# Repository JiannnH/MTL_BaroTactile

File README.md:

# MTL_BaroTactile

**A cost-efficient, repairable barometric tactile sensor**

## Highlights

- **Low cost:** material cost below **80 USD**, built from 16 MPL3115A2 MEMS barometers on a single PCB.
- **Repairable:** the rubber layer is molded **separately** rather than over the barometers, then clamped on by a 3D-printed frame, so a worn surface can be swapped in minutes.

## Sensor Design

The sensor has three layers:

1. **PCB**: 16 MPL3115A2 barometers in a 1D array, read through a multiplexer.
2. **Rubber**: a VytaFlex 40 strip cast in a 3D-printed mold.
3. **Frame**: a 3D-printed clamp bolted to the PCB that holds the rubber in place.

## Demo: Real-Time Localization on the E-TRoll Gripper

The sensor is mounted on one finger of the open-source
[**E-TRoll gripper**](https://www.imperial.ac.uk/manipulation-touch/open-source/hardware/e-troll/)
from the Manipulation and Touch Lab. The gripper rolls a cube and a cylinder across the
sensing surface, and the tactile estimate (black) closely tracks the camera-based ground truth (green).
The video plays at 10× speed.

## Repository Structure

- **[Code](Code/)**: Arduino code for the sensor (MPL3115A2) and the testing rig
- **[Hardware](Hardware/)**: PCB designs, 3D CAD files and testing rig hardware
  - **[PCB/MTL_BaroTactile_MPL3115A2](Hardware/PCB/MTL_BaroTactile_MPL3115A2/)**: main sensor version (used in the paper)
  - **[PCB/MTL_BaroTactile_MS5840](Hardware/PCB/MTL_BaroTactile_MS5840/)**: alternative version with the MS5840
  - **[Mold](Hardware/Mold/)**: rubber mold and frame CAD for fabrication
  - **[TestingRig](Hardware/TestingRig/)**: automated indentation rig for data collection

## Hardware Versions

### MPL3115A2 Version (Paper Implementation)
The primary sensor design, built with the MPL3115A2 barometric pressure sensor.

### MS5840 Version (Alternative)
An alternative design built with the MS5840 barometer. Use it when the MPL3115A2 is out of stock; it gives comparable performance for barometric tactile sensing.

## Fabrication Overview

1. 3D print the rubber mold and apply mold release spray.
2. Mix parts A and B of Smooth-On VytaFlex 40, de-gas the mixture, and pour it into the mold.
3. Close the mold and let it cure for at least 1 day, then remove the rubber.
4. Reflow-solder the components onto the PCB.
5. Place the rubber on the PCB, then bolt the 3D-printed frame over it until the rubber is held securely.

## Citation

If you use this work in your research, please cite our paper:

```bibtex
@ARTICLE{10770605,
  author={Hou, Jian and Zhou, Xin and Spiers, Adam},
  journal={IEEE Transactions on Robotics},
  title={Location and Orientation Super-Resolution Sensing With a Cost-Efficient and Repairable Barometric Tactile Sensor},
  year={2025},
  volume={41},
  pages={729-741},
  doi={10.1109/TRO.2024.3508315}
}
```

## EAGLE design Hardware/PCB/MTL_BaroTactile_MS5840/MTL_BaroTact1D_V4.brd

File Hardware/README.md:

# Hardware Design

This folder contains the hardware design files.

## Folder Structure

The repository is organized into the following folders:

**PCB Design**: This folder contains schematics and layout files for our PCB. *PCB/MTL_BaroTactile_MPL3115A2/MTL_BaroTact1D_V3* is the one we used for super-resolution. *PCB/MTL_BaroTactile_MS5840/MTL_BaroTact1D_V4* is a new PCB design, which uses the MS-5840 barometer instead of the MPL3115A2 (stopped manufacturing).

**Testing Rig Design**: In this folder, you'll find the 3D-printed components on our testing rig.

**Mold**: This folder contains CAD files related to the mold used in the manufacturing process and assembly method of rubber components and sensors within our hardware.

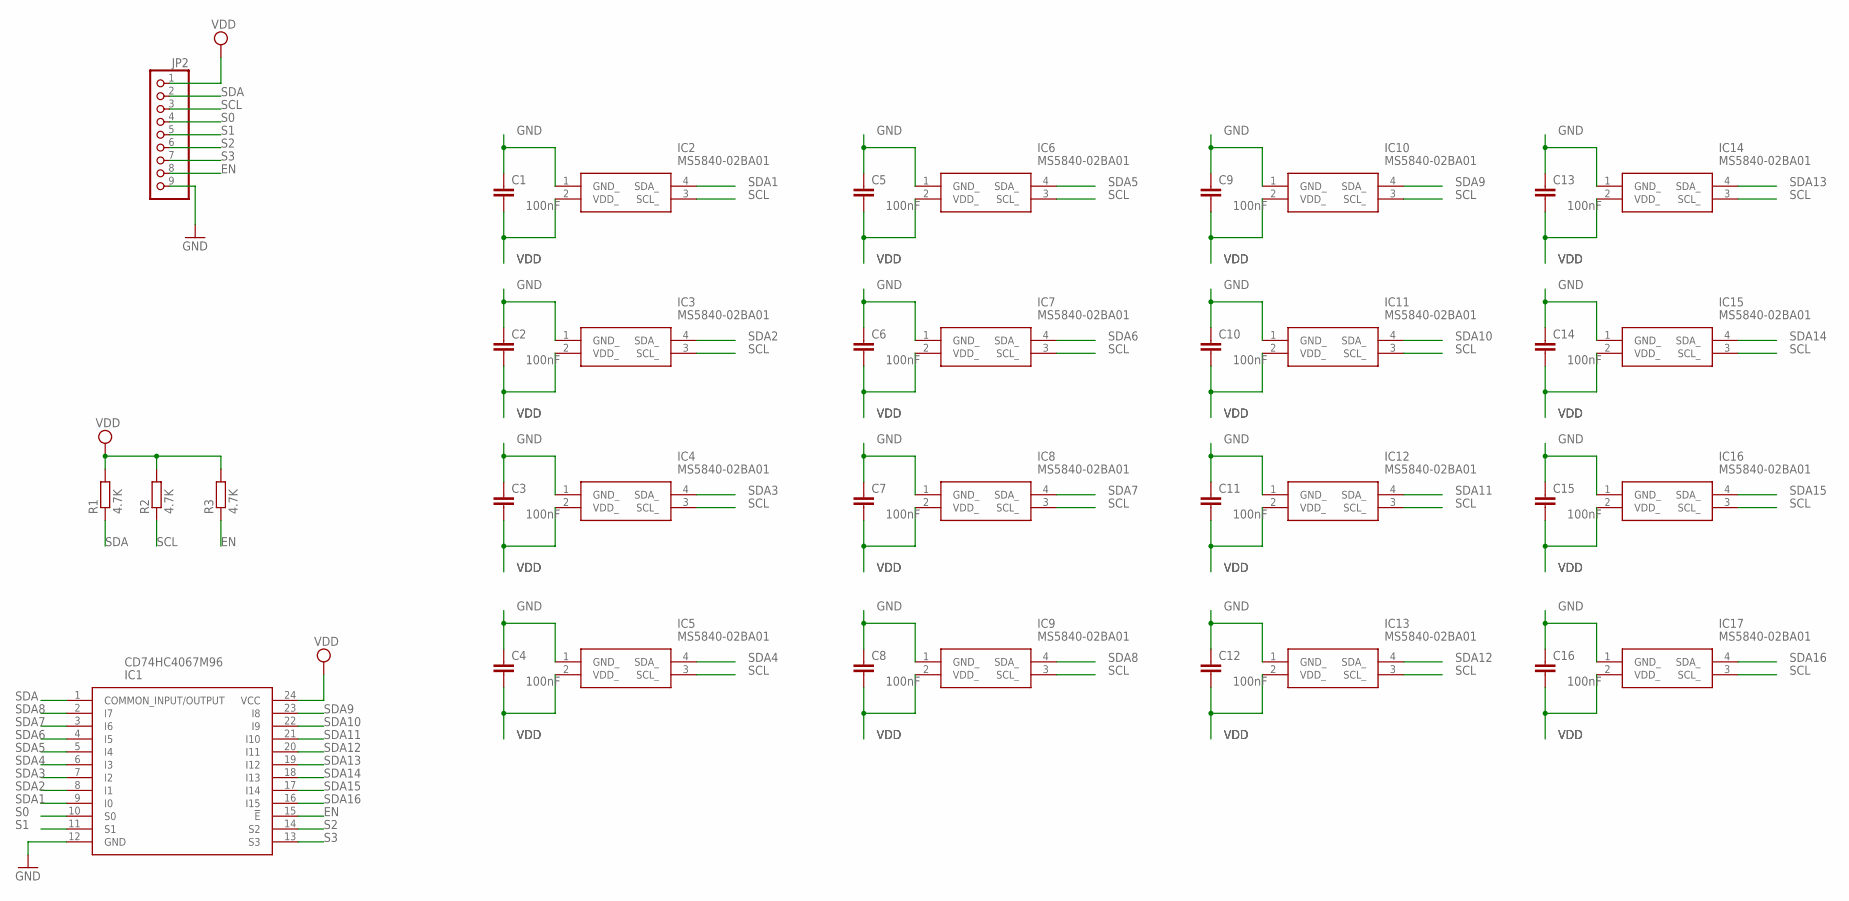
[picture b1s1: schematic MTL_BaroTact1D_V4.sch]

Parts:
C1, C2, C3, C4, C5, C6, C7, C8, C9, C10, C11, C12, C13, C14, C15, C16: 100nF; C0603
IC1: CD74HC4067M96; SOIC127P1030X265-24N
IC2, IC3, IC4, IC5, IC6, IC7, IC8, IC9, IC10, IC11, IC12, IC13, IC14, IC15, IC16, IC17: MS5840-02BA01; MS584002BA01
JP2: PINHD-1X9; 1X09
R1, R2, R3: 4.7K; R0603

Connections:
EN: IC1.15 (!E), JP2.8, R3.1
GND: C1.1, C2.1, C3.1, C4.1, C5.1, C6.1, C7.1, C8.1, C9.1, C10.1, C11.1, C12.1, C13.1, C14.1, C15.1, C16.1, IC1.12 (GND), IC2.1 (GND_), IC3.1 (GND_), IC4.1 (GND_), IC5.1 (GND_), IC6.1 (GND_), IC7.1 (GND_), IC8.1 (GND_), IC9.1 (GND_), IC10.1 (GND_), IC11.1 (GND_), IC12.1 (GND_), IC13.1 (GND_), IC14.1 (GND_), IC15.1 (GND_), IC16.1 (GND_), IC17.1 (GND_), JP2.9
S0: IC1.10 (S0), JP2.4
S1: IC1.11 (S1), JP2.5
S2: IC1.14 (S2), JP2.6
S3: IC1.13 (S3), JP2.7
SCL: IC2.3 (SCL_), IC3.3 (SCL_), IC4.3 (SCL_), IC5.3 (SCL_), IC6.3 (SCL_), IC7.3 (SCL_), IC8.3 (SCL_), IC9.3 (SCL_), IC10.3 (SCL_), IC11.3 (SCL_), IC12.3 (SCL_), IC13.3 (SCL_), IC14.3 (SCL_), IC15.3 (SCL_), IC16.3 (SCL_), IC17.3 (SCL_), JP2.3, R2.1
SDA: IC1.1 (COMMON_INPUT/OUTPUT), JP2.2, R1.1
SDA1: IC1.9 (I0), IC2.4 (SDA_)
SDA2: IC1.8 (I1), IC3.4 (SDA_)
SDA3: IC1.7 (I2), IC4.4 (SDA_)
SDA4: IC1.6 (I3), IC5.4 (SDA_)
SDA5: IC1.5 (I4), IC6.4 (SDA_)
SDA6: IC1.4 (I5), IC7.4 (SDA_)
SDA7: IC1.3 (I6), IC8.4 (SDA_)
SDA8: IC1.2 (I7), IC9.4 (SDA_)
SDA9: IC1.23 (I8), IC10.4 (SDA_)
SDA10: IC1.22 (I9), IC11.4 (SDA_)
SDA11: IC1.21 (I10), IC12.4 (SDA_)
SDA12: IC1.20 (I11), IC13.4 (SDA_)
SDA13: IC1.19 (I12), IC14.4 (SDA_)
SDA14: IC1.18 (I13), IC15.4 (SDA_)
SDA15: IC1.17 (I14), IC16.4 (SDA_)
SDA16: IC1.16 (I15), IC17.4 (SDA_)
VDD: C1.2, C2.2, C3.2, C4.2, C5.2, C6.2, C7.2, C8.2, C9.2, C10.2, C11.2, C12.2, C13.2, C14.2, C15.2, C16.2, IC1.24 (VCC), IC2.2 (VDD_), IC3.2 (VDD_), IC4.2 (VDD_), IC5.2 (VDD_), IC6.2 (VDD_), IC7.2 (VDD_), IC8.2 (VDD_), IC9.2 (VDD_), IC10.2 (VDD_), IC11.2 (VDD_), IC12.2 (VDD_), IC13.2 (VDD_), IC14.2 (VDD_), IC15.2 (VDD_), IC16.2 (VDD_), IC17.2 (VDD_), JP2.1, R1.2, R2.2, R3.2

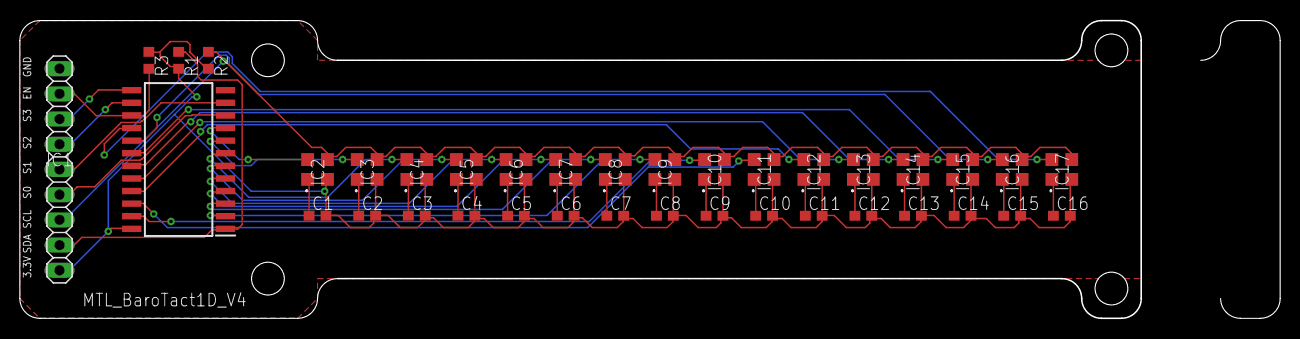
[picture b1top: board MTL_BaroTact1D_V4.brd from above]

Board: 2 copper layers, 126.8 x 30.0 mm, 37 parts (0 on the bottom side), 25 nets.

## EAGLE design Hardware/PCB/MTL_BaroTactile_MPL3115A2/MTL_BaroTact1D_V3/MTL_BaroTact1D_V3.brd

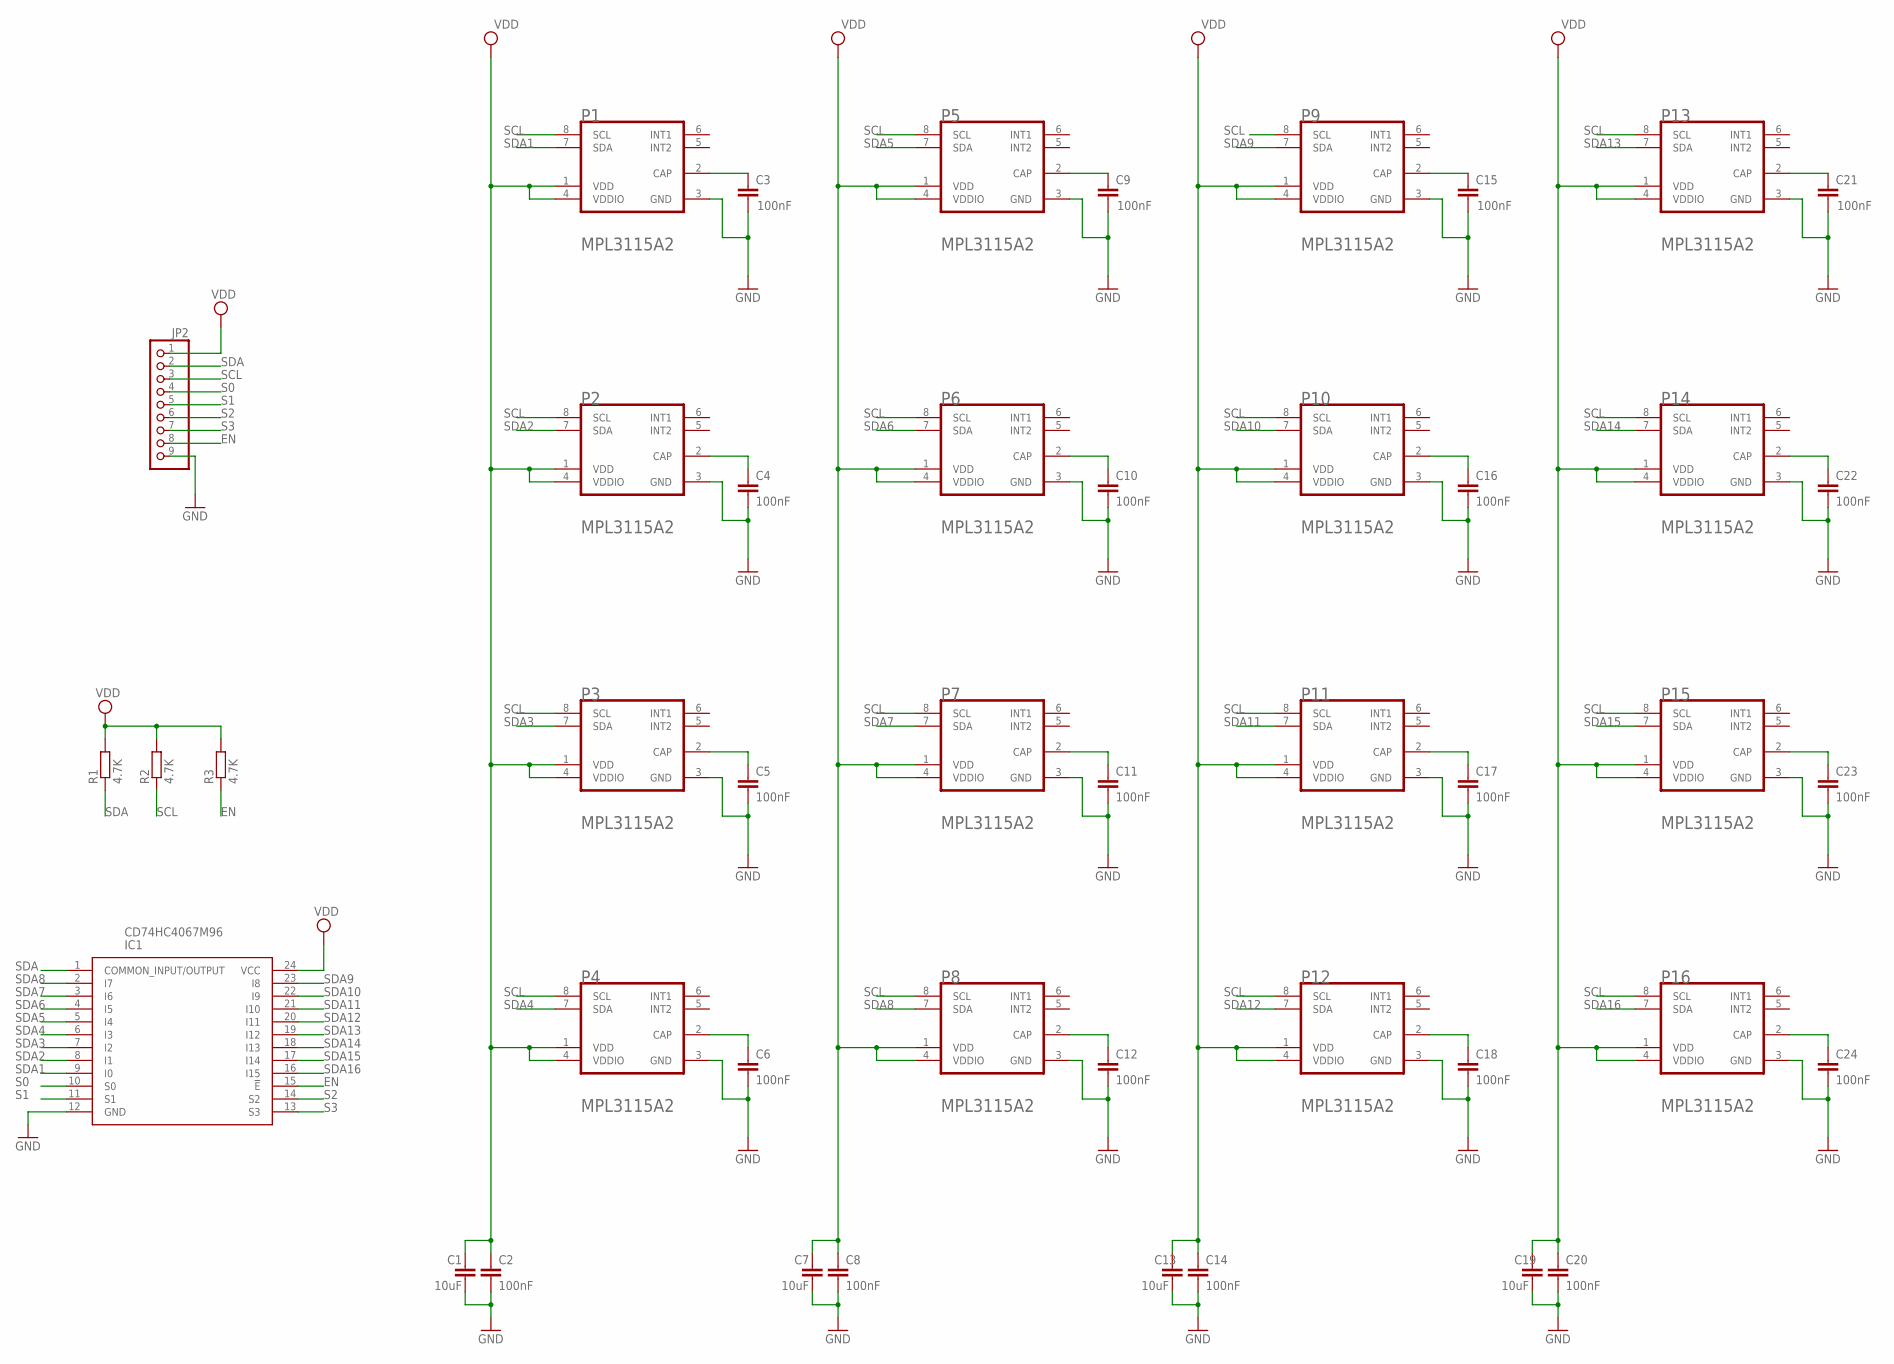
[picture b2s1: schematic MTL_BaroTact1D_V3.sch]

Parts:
C1, C7, C13, C19: 10uF; C0603
C2, C3, C4, C5, C6, C8, C9, C10, C11, C12, C14, C15, C16, C17, C18, C20, C21, C22, C23, C24: 100nF; C0603
IC1: CD74HC4067M96; SOIC127P1030X265-24N
JP2: PINHD-1X9; 1X09
P1, P2, P3, P4, P5, P6, P7, P8, P9, P10, P11, P12, P13, P14, P15, P16: FREESCALE_SEMICONDUCTOR_MPL3115A2FREESCALE_SEMICO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; FREESCALE_SEMICONDUCTOR_MPL3115A2_0
R1, R2, R3: 4.7K; R0603

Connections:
EN: IC1.15 (!E), JP2.8, R3.1
GND: C1.2, C2.2, C3.2, C4.2, C5.2, C6.2, C7.2, C8.2, C9.2, C10.2, C11.2, C12.2, C13.2, C14.2, C15.2, C16.2, C17.2, C18.2, C19.2, C20.2, C21.2, C22.2, C23.2, C24.2, IC1.12 (GND), JP2.9, P1.3 (GND), P2.3 (GND), P3.3 (GND), P4.3 (GND), P5.3 (GND), P6.3 (GND), P7.3 (GND), P8.3 (GND), P9.3 (GND), P10.3 (GND), P11.3 (GND), P12.3 (GND), P13.3 (GND), P14.3 (GND), P15.3 (GND), P16.3 (GND)
unnamed: C3.1, P1.2 (CAP)
unnamed: C4.1, P2.2 (CAP)
unnamed: C9.1, P5.2 (CAP)
unnamed: C10.1, P6.2 (CAP)
unnamed: C11.1, P7.2 (CAP)
unnamed: C12.1, P8.2 (CAP)
unnamed: C5.1, P3.2 (CAP)
unnamed: C6.1, P4.2 (CAP)
unnamed: C15.1, P9.2 (CAP)
unnamed: C16.1, P10.2 (CAP)
unnamed: C17.1, P11.2 (CAP)
unnamed: C18.1, P12.2 (CAP)
unnamed: C21.1, P13.2 (CAP)
unnamed: C22.1, P14.2 (CAP)
unnamed: C23.1, P15.2 (CAP)
unnamed: C24.1, P16.2 (CAP)
S0: IC1.10 (S0), JP2.4
S1: IC1.11 (S1), JP2.5
S2: IC1.14 (S2), JP2.6
S3: IC1.13 (S3), JP2.7
SCL: JP2.3, P1.8 (SCL), P2.8 (SCL), P3.8 (SCL), P4.8 (SCL), P5.8 (SCL), P6.8 (SCL), P7.8 (SCL), P8.8 (SCL), P9.8 (SCL), P10.8 (SCL), P11.8 (SCL), P12.8 (SCL), P13.8 (SCL), P14.8 (SCL), P15.8 (SCL), P16.8 (SCL), R2.1
SDA: IC1.1 (COMMON_INPUT/OUTPUT), JP2.2, R1.1
SDA1: IC1.9 (I0), P1.7 (SDA)
SDA2: IC1.8 (I1), P2.7 (SDA)
SDA3: IC1.7 (I2), P3.7 (SDA)
SDA4: IC1.6 (I3), P4.7 (SDA)
SDA5: IC1.5 (I4), P5.7 (SDA)
SDA6: IC1.4 (I5), P6.7 (SDA)
SDA7: IC1.3 (I6), P7.7 (SDA)
SDA8: IC1.2 (I7), P8.7 (SDA)
SDA9: IC1.23 (I8), P9.7 (SDA)
SDA10: IC1.22 (I9), P10.7 (SDA)
SDA11: IC1.21 (I10), P11.7 (SDA)
SDA12: IC1.20 (I11), P12.7 (SDA)
SDA13: IC1.19 (I12), P13.7 (SDA)
SDA14: IC1.18 (I13), P14.7 (SDA)
SDA15: IC1.17 (I14), P15.7 (SDA)
SDA16: IC1.16 (I15), P16.7 (SDA)
VDD: C1.1, C2.1, C7.1, C8.1, C13.1, C14.1, C19.1, C20.1, IC1.24 (VCC), JP2.1, P1.1 (VDD), P1.4 (VDDIO), P2.1 (VDD), P2.4 (VDDIO), P3.1 (VDD), P3.4 (VDDIO), P4.1 (VDD), P4.4 (VDDIO), P5.1 (VDD), P5.4 (VDDIO), P6.1 (VDD), P6.4 (VDDIO), P7.1 (VDD), P7.4 (VDDIO), P8.1 (VDD), P8.4 (VDDIO), P9.1 (VDD), P9.4 (VDDIO), P10.1 (VDD), P10.4 (VDDIO), P11.1 (VDD), P11.4 (VDDIO), P12.1 (VDD), P12.4 (VDDIO), P13.1 (VDD), P13.4 (VDDIO), P14.1 (VDD), P14.4 (VDDIO), P15.1 (VDD), P15.4 (VDDIO), P16.1 (VDD), P16.4 (VDDIO), R1.2, R2.2, R3.2

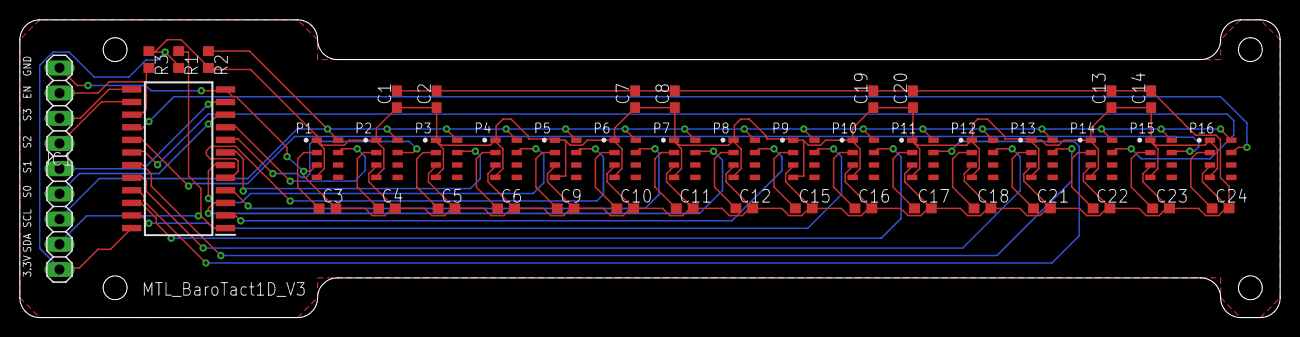
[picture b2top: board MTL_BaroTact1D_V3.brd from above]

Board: 2 copper layers, 127.0 x 30.0 mm, 45 parts (0 on the bottom side), 41 nets.
